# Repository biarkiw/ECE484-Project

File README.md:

# ECE484-Project
Project files for the ECE 484 project, allong with the hardware desgin files for the RPi Pico DSP Hat

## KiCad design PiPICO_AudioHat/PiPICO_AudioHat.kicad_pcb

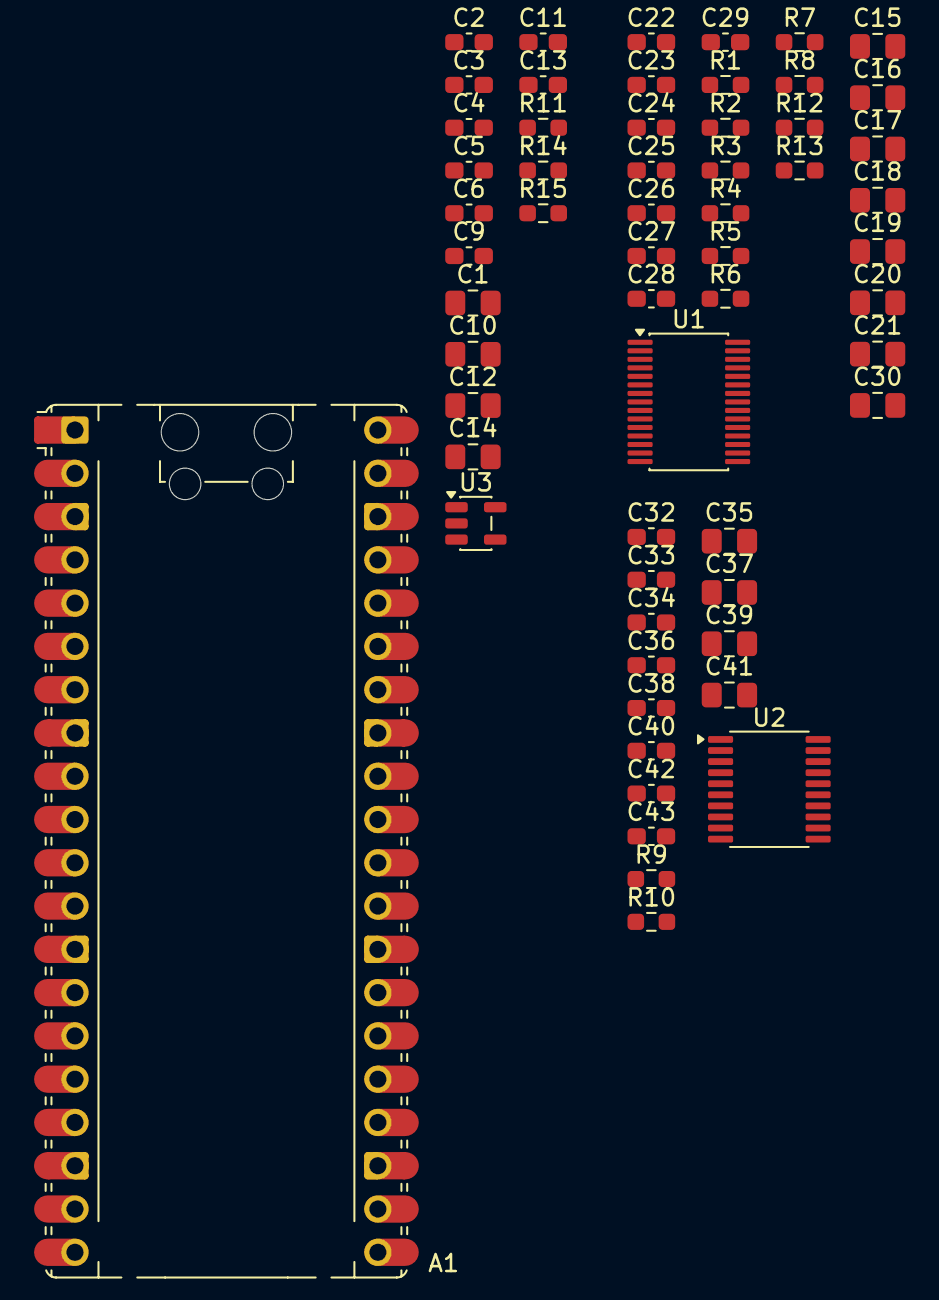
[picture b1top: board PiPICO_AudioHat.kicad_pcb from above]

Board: 2 copper layers, 59 parts (0 on the bottom side), 34 nets, no tracks yet.

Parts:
A1: RaspberryPi_Pico; RaspberryPi_Pico_Common_Unspecified
C1, C10, C12, C14, C15, C16, C17, C18, C19, C20, C21, C30, C35, C37, C39, C41: 10uF; C_0805_2012Metric_Pad1.18x1.45mm_HandSolder
C2, C3: 1uF; C_0603_1608Metric_Pad1.08x0.95mm_HandSolder
C4, C5, C6, C9, C11, C13, C34, C36, C38, C40: 0.1uF; C_0603_1608Metric_Pad1.08x0.95mm_HandSolder
C22, C23, C24, C25, C26, C27, C28, C29: 0.01uF; C_0603_1608Metric_Pad1.08x0.95mm_HandSolder
C32, C33: 2.2uF; C_0603_1608Metric_Pad1.08x0.95mm_HandSolder
C42, C43: 2.2bF; C_0603_1608Metric_Pad1.08x0.95mm_HandSolder
R1, R2, R3, R4, R5, R6, R7, R8: 100 Ohm; R_0603_1608Metric_Pad0.98x0.95mm_HandSolder
R9, R10: 470; R_0603_1608Metric_Pad0.98x0.95mm_HandSolder
R11: 1M; R_0603_1608Metric_Pad0.98x0.95mm_HandSolder
R12, R13: R_Small; R_0603_1608Metric_Pad0.98x0.95mm_HandSolder
R14, R15: 5.1k; R_0603_1608Metric_Pad0.98x0.95mm_HandSolder
U1: PCM1860DBT; TSSOP-30_4.4x7.8mm_P0.5mm
U2: PCM5101A; TSSOP-20_4.4x6.5mm_P0.65mm
U3: AP2112K-3.3; SOT-23-5

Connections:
+3.3VA: A1.35 (ADC_VREF), C9.2, C10.1, C11.2, C12.1, C13.2, C14.1, C36.1, C37.1, C38.1, C39.1, U1.8 (AVDD), U2.1 (CPVDD), U2.8 (AVDD)
+3V3: A1.39 (VSYS), C3.1, C40.1, C41.1, U1.13 (DVDD), U1.14 (IOVDD), U2.20 (DVDD), U3.5 (VOUT)
/ADC/Aud_Form: R13.2, U1.22 (MD4)
/ADC/Filt_Sel: R12.2, U1.24 (MD3)
/ADC/VIN_L1: C23.2, R1.2, U1.3 (VINL1/VIN1P)
/ADC/VIN_L2: C25.2, R3.2, U1.1 (VINL2/VIN1M)
/ADC/VIN_L3: C27.2, R5.2, U1.29 (VINL3/VIN4P)
/ADC/VIN_L4: C29.2, R7.2, U1.27 (VINL4/VIN4M)
/ADC/VIN_R1: C24.2, R2.2, U1.4 (VINR1/VIN2P)
/ADC/VIN_R2: C26.2, R4.2, U1.2 (VINR2/VIN2M)
/ADC/VIN_R3: C28.2, R6.2, U1.30 (VINR3/VIN3P)
/ADC/VIN_R4: C22.2, R8.2, U1.28 (VINR4/VIN3M)
/DAC/L_CH: C42.1, R9.2
/DAC/R_CH: C43.1, R10.2
GND: A1.3 (GND), A1.8 (GND), A1.13 (GND), A1.18 (GND), A1.23 (GND), A1.28 (GND), A1.38 (GND), C1.2, C2.2, C3.2, C34.2, C35.2, C40.2, C41.2, R11.2, R14.2, R15.2, U1.12 (DGND), U2.10 (DEMP), U2.11 (FLT), U2.16 (FMT), U2.19 (DGND), U3.2 (GND)
GNDA: A1.33 (AGND), C4.2, C5.2, C6.2, C9.1, C10.2, C11.1, C12.2, C13.1, C14.2, C22.1, C23.1, C24.1, C25.1, C26.1, C27.1, C28.1, C29.1, C32.2, C33.2, C36.2, C37.2, C38.2, C39.2, C42.2, C43.2, U1.7 (AGND), U2.2 (CAPP), U2.3 (CPGND), U2.9 (AGND)
unnamed: A1.31 (GPIO26_ADC0), C4.1
unnamed: A1.32 (GPIO27_ADC1), C5.1
unnamed: A1.34 (GPIO28_ADC2), C6.1
unnamed: C15.2, R1.1
unnamed: C16.2, R2.1
unnamed: C17.2, R3.1
unnamed: C18.2, R4.1
unnamed: C19.2, R5.1
unnamed: C20.2, R6.1
unnamed: C21.2, R7.1
unnamed: C30.2, R8.1
unnamed: C1.1, C2.1, U3.1 (VIN)
unnamed: R11.1, U3.3 (EN)
unnamed: C32.1, U2.4 (CAPM)
unnamed: C34.1, C35.1, U2.18 (LDOO)
unnamed: R9.1, U2.6 (OUTL)
unnamed: R10.1, U2.7 (OUTR)
unnamed: C33.1, U2.5 (VNEG)
